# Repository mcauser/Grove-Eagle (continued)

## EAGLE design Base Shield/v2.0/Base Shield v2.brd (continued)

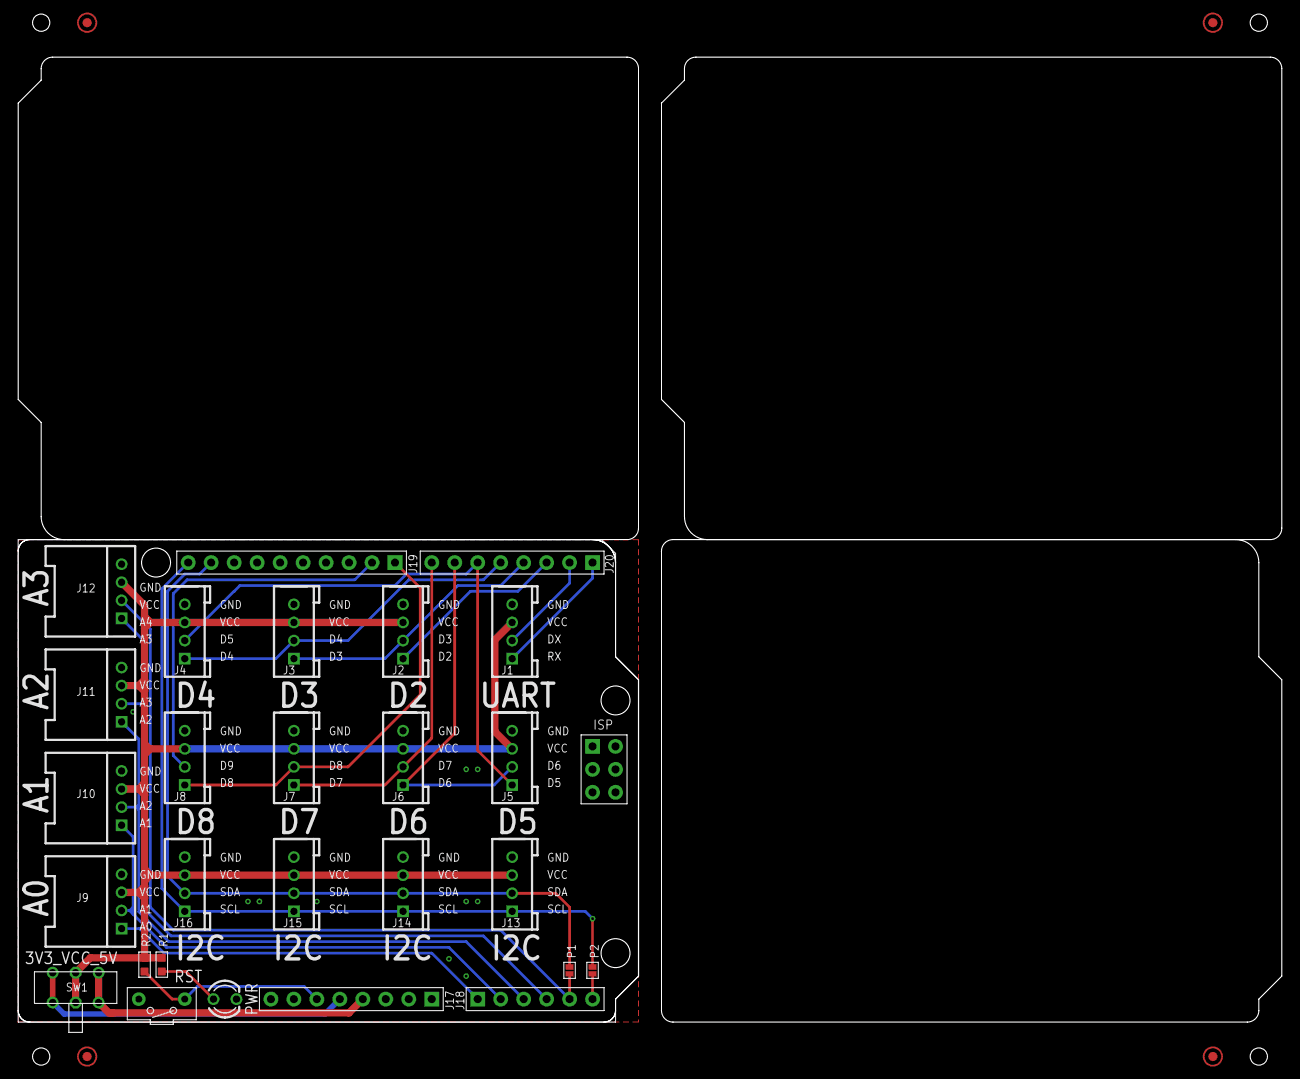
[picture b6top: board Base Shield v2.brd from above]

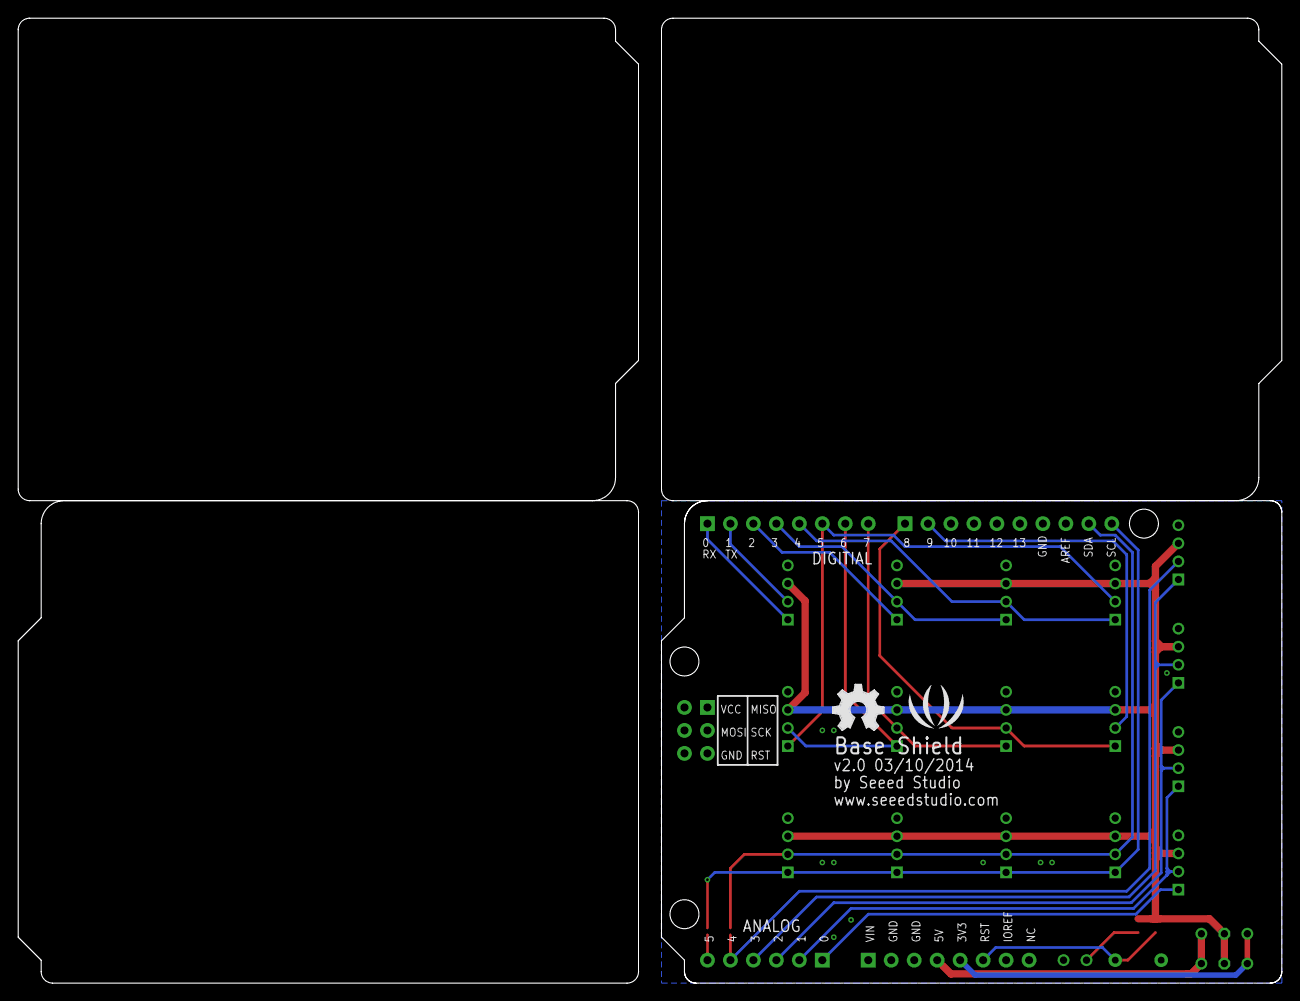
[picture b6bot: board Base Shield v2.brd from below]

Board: 2 copper layers, 139.7 x 106.7 mm, 30 parts (2 on the bottom side), 24 nets.

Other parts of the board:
U$2: OSHW_FILLX200_NOTEXT
U$4: LOGO_SILK

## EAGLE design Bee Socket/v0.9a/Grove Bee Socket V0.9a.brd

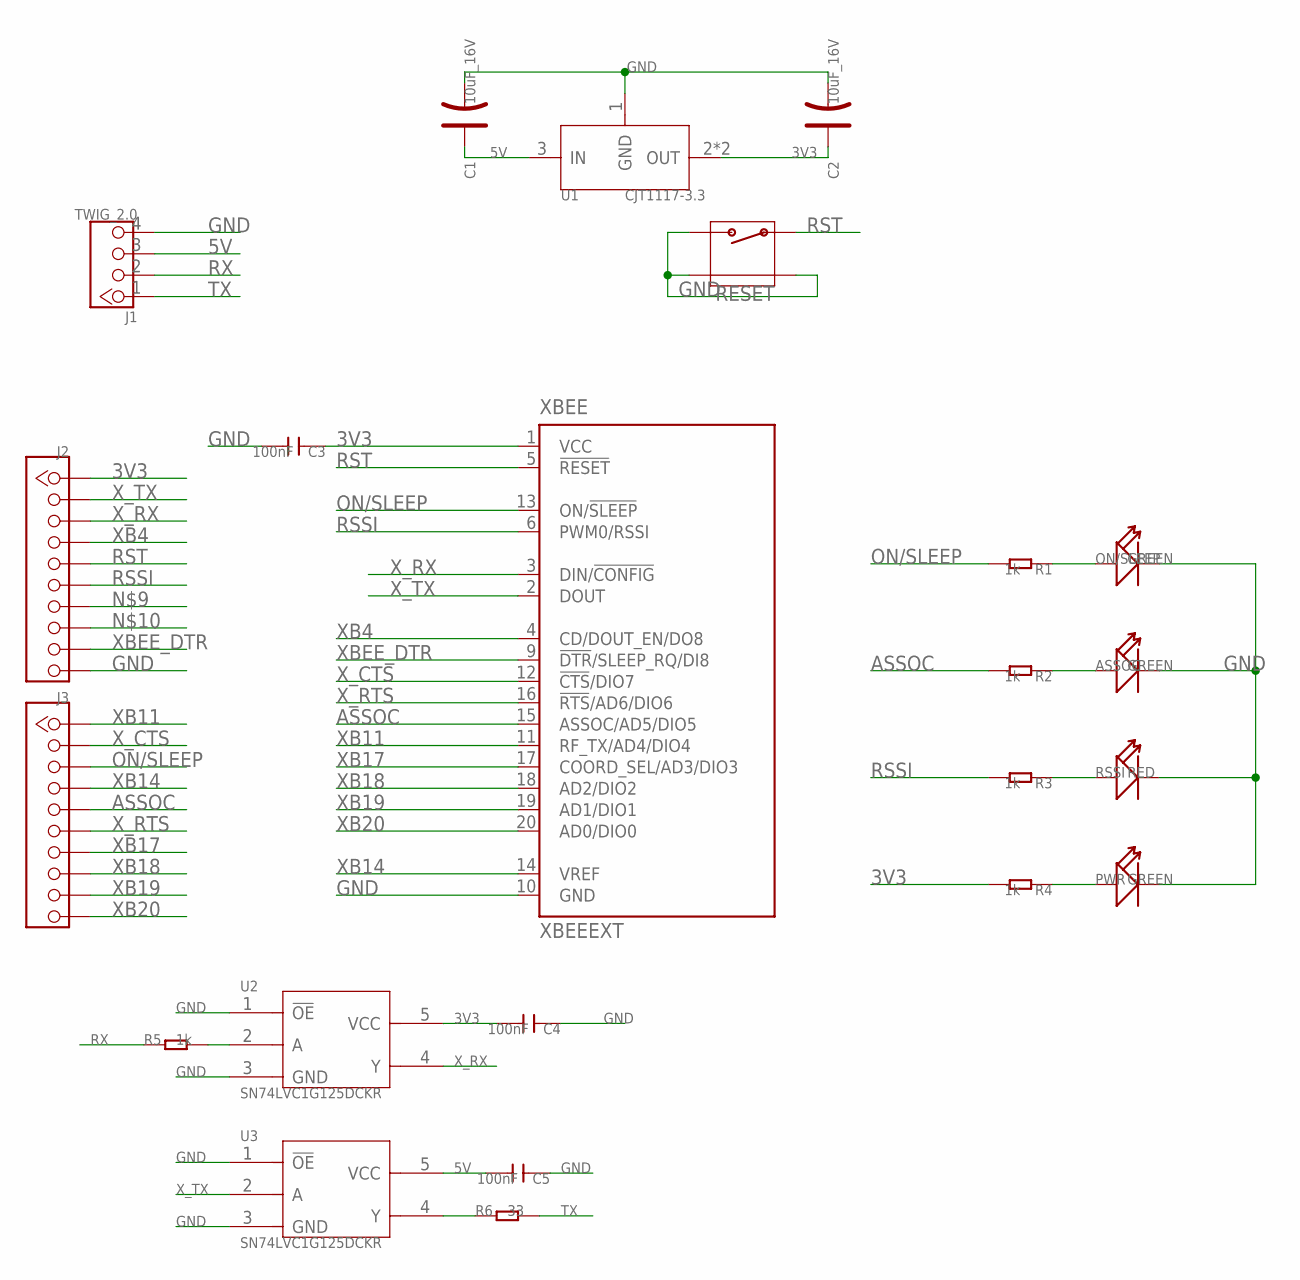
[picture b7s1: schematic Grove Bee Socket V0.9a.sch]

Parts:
ASSOC: GREEN; LED-0603
C1, C2: 10uF_16V; AVX-A
C3, C4, C5: 100nF; C0603
J1: TWIG_2.0; 2.0_1X4
J2, J3: DNP; CK1X10
ON/SLEEP: GREEN; LED-0603
PWR: GREEN; LED-0603
R1, R2, R3, R4, R5: 1k; R0603
R6: 33; R0603
RESET: FOR_TEST_ALBERT_V6_BUTTON_4P_SMD; FOR_TEST_ALBERT_V6_4P-SMD-7X3.5X3.5
RSSI: RED; LED-0603
U1: CJT1117-3.3; SOT-223
U2, U3: SN74LVC1G125DCKR; SOT353
XBEE: XBEEEXT; XBEE_PLUG

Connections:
3V3: C2.+, C3.1, C4.2, J2.1, R4.2, U1.2 (OUT), U1.TER (OUT), U2.5 (VCC), XBEE.1 (VCC)
5V: C1.+, C5.2, J1.3, U1.3 (IN), U3.5 (VCC)
ASSOC: J3.5, R2.2, XBEE.15 (ASSOC/AD5/DIO5)
GND: ASSOC.-, C1.-, C2.-, C3.2, C4.1, C5.1, J1.4, J2.10, ON/SLEEP.-, PWR.-, RESET.2, RESET.S1, RESET.S2, RSSI.-, U1.1 (GND), U2.1 (!OE!), U2.3 (GND), U3.1 (!OE!), U3.3 (GND), XBEE.10 (GND)
unnamed: R6.1, U3.4 (Y)
unnamed: ON/SLEEP.+, R1.1
unnamed: ASSOC.+, R2.1
unnamed: R3.1, RSSI.+
unnamed: PWR.+, R4.1
unnamed: R5.2, U2.2 (A)
ON/SLEEP: J3.3, R1.2, XBEE.13 (ON/!SLEEP)
RSSI: J2.6, R3.2, XBEE.6 (PWM0/RSSI)
RST: J2.5, RESET.1, XBEE.5 (!RESET)
RX: J1.2, R5.1
TX: J1.1, R6.2
XB4: J2.4, XBEE.4 (CD/DOUT_EN/DO8)
XB11: J3.1, XBEE.11 (RF_TX/AD4/DIO4)
XB14: J3.4, XBEE.14 (VREF)
XB17: J3.7, XBEE.17 (COORD_SEL/AD3/DIO3)
XB18: J3.8, XBEE.18 (AD2/DIO2)
XB19: J3.9, XBEE.19 (AD1/DIO1)
XB20: J3.10, XBEE.20 (AD0/DIO0)
XBEE_DTR: J2.9, XBEE.9 (!DTR!/SLEEP_RQ/DI8)
X_CTS: J3.2, XBEE.12 (!CTS!/DIO7)
X_RTS: J3.6, XBEE.16 (!RTS!/AD6/DIO6)
X_RX: J2.3, U2.4 (Y), XBEE.3 (DIN/!CONFIG)
X_TX: J2.2, U3.2 (A), XBEE.2 (DOUT)

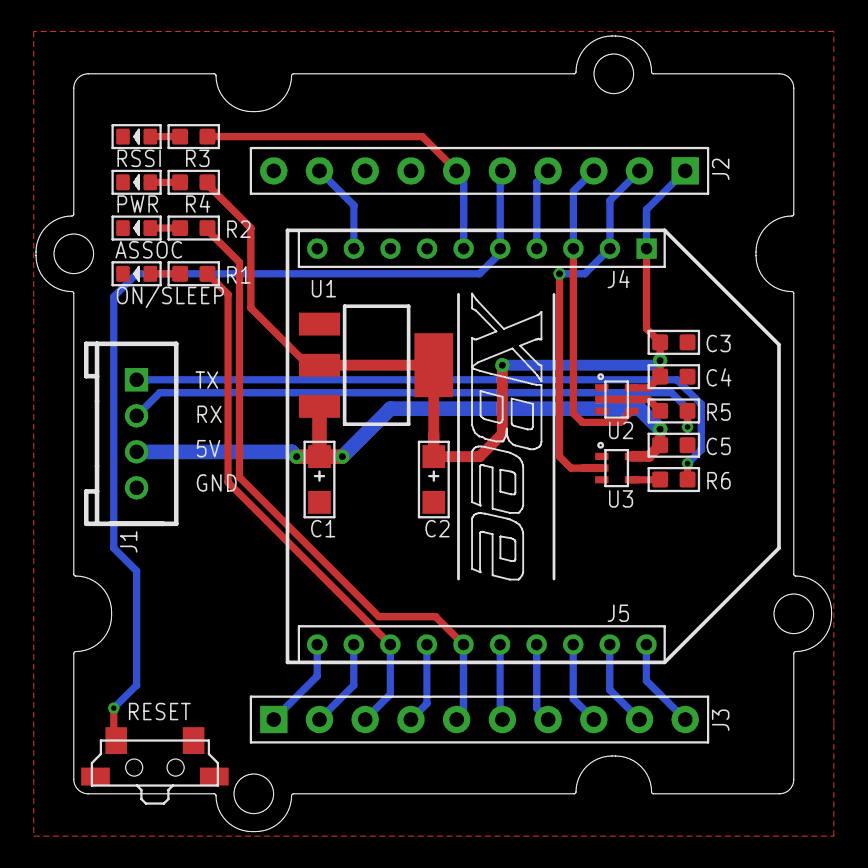
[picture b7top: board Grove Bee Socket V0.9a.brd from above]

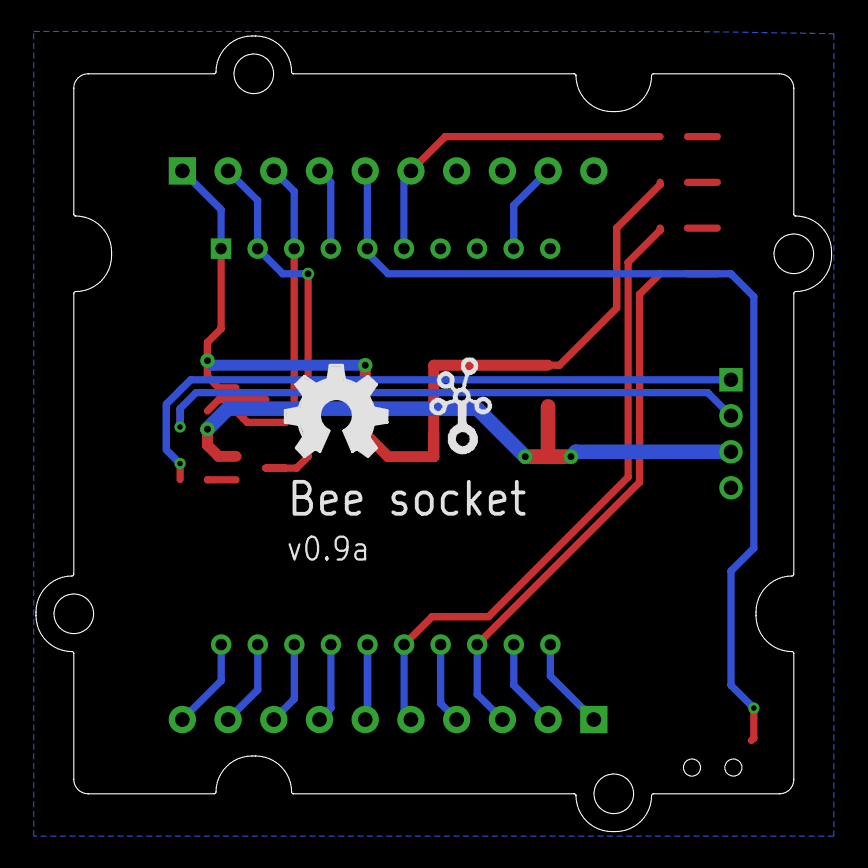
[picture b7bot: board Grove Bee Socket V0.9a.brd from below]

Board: 2 copper layers, 44.2 x 44.2 mm, 26 parts (2 on the bottom side), 27 nets.

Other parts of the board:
U$1: OSHW_FILLX200_NOTEXT
U$2: 2X2U-DIM-W/-DRILL
U$3: TWIGLOGO_SMALL
